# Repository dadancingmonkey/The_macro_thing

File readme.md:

a cool little macro pad for my desk!

This is sort of inspired by spotify's The Car Thing, hence the name. 

while I am familiar with my 3d modeling software, onshape, and i have been 3d printing for the past couple of months since i got my printer, this is my first project that involves electronics. 
This project was the first time i've ever used Kicad, and through following guides and tutorials on youtube, i was able to cobble together my own little macropad!

the assembly:

the top blue part is jsut a press fit:

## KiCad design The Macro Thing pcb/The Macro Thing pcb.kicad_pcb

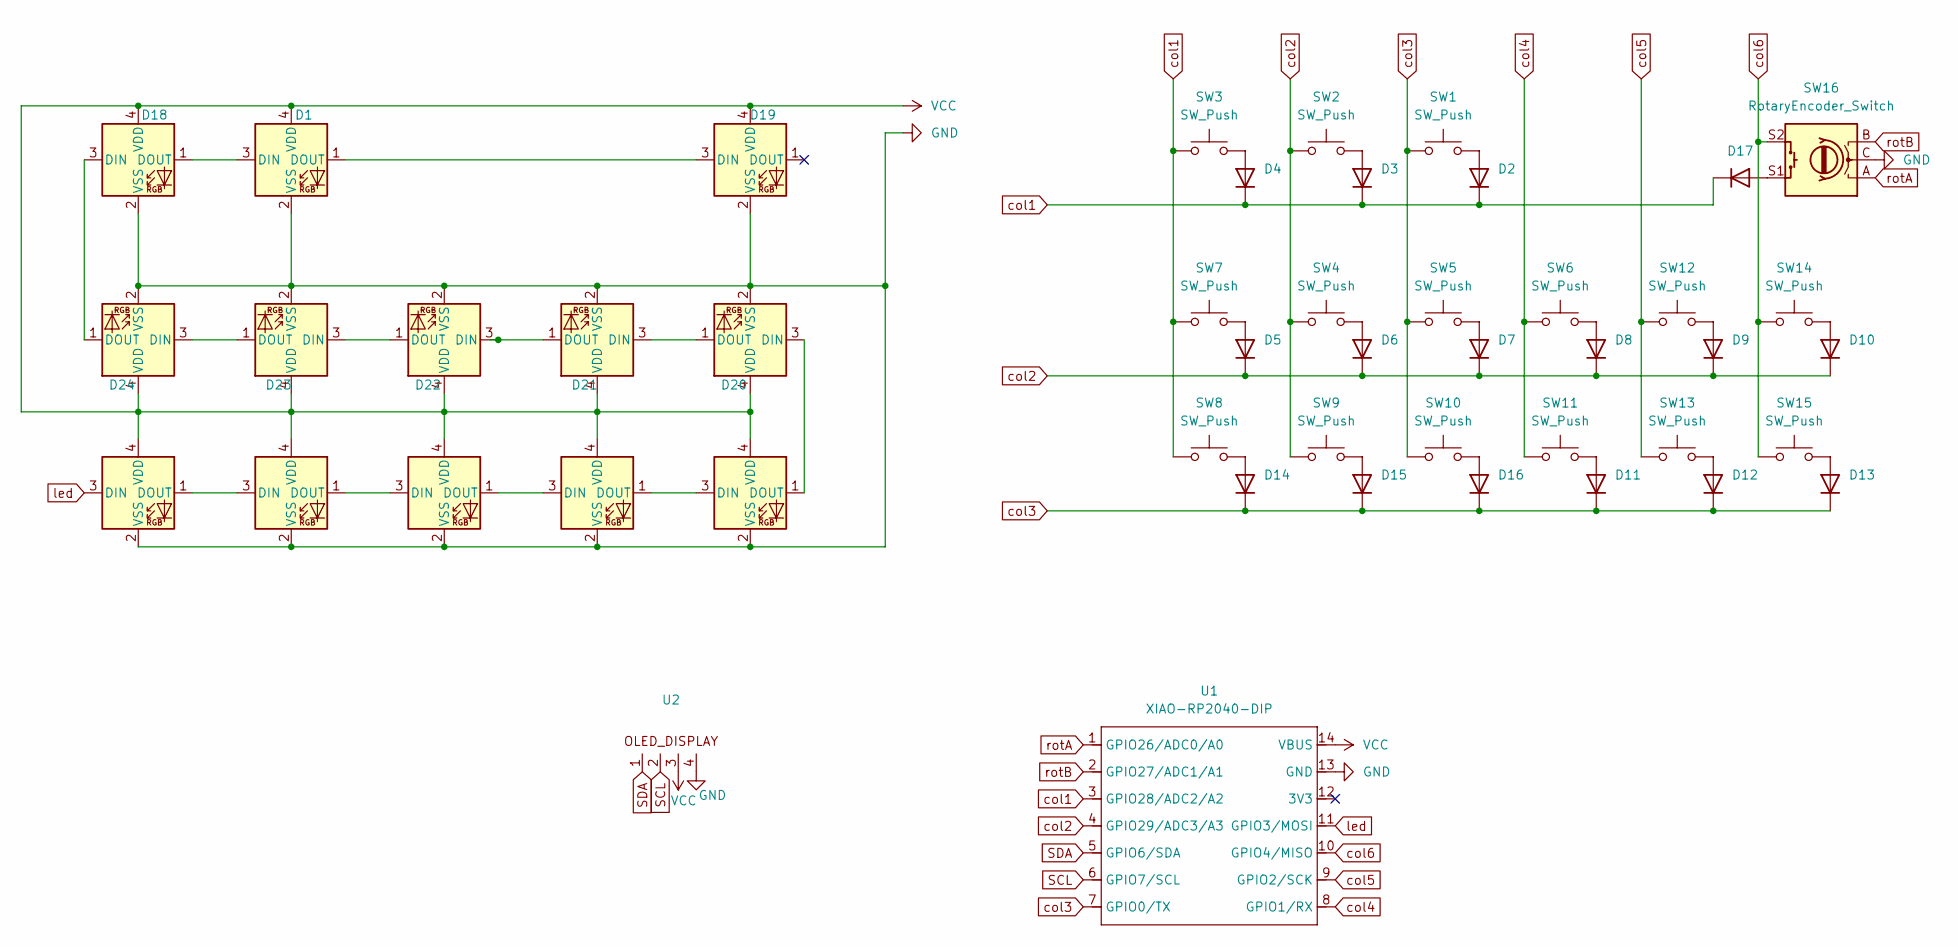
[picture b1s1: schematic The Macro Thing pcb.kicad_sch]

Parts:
D1, D18, D19, D20, D21, D22, D23, D24, D25, D26, D27, D28, D29: SK6812MINI; LED_SK6812MINI_PLCC4_3.5x3.5mm_P1.75mm
D2, D3, D4, D5, D6, D7, D8, D9, D10, D11, D12, D13, D14, D15, D16, D17: 1N4148WT; D_DO-35_SOD27_P7.62mm_Horizontal
SW1, SW2, SW3, SW4, SW5, SW6, SW7, SW8, SW9, SW10, SW11, SW12, SW13, SW14, SW15: SW_Push; SW_Cherry_MX_1.00u_PCB
SW16: RotaryEncoder_Switch; RotaryEncoder_Alps_EC11E-Switch_Vertical_H20mm
U1: XIAO-RP2040-DIP
U2: PinHeader_1x04_P2.54mm_Vertical

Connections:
GND: D1.2 (VSS), D18.2 (VSS), D19.2 (VSS), D20.2 (VSS), D21.2 (VSS), D22.2 (VSS), D23.2 (VSS), D24.2 (VSS), D25.2 (VSS), D26.2 (VSS), D27.2 (VSS), D28.2 (VSS), D29.2 (VSS), SW16.C, U1.13 (GND), U2.4
unnamed: D1.3 (DIN), D18.1 (DOUT)
unnamed: D1.1 (DOUT), D19.3 (DIN)
unnamed: D2.2 (A), SW1.2
unnamed: D3.2 (A), SW2.2
unnamed: D4.2 (A), SW3.2
unnamed: D5.2 (A), SW7.2
unnamed: D6.2 (A), SW4.2
unnamed: D7.2 (A), SW5.2
unnamed: D8.2 (A), SW6.2
unnamed: D9.2 (A), SW12.2
unnamed: D10.2 (A), SW14.2
unnamed: D11.2 (A), SW11.2
unnamed: D12.2 (A), SW13.2
unnamed: D13.2 (A), SW15.2
unnamed: D14.2 (A), SW8.2
unnamed: D15.2 (A), SW9.2
unnamed: D16.2 (A), SW10.2
unnamed: D17.2 (A), SW16.S1
unnamed: D18.3 (DIN), D24.1 (DOUT)
unnamed: D20.3 (DIN), D29.1 (DOUT)
unnamed: D20.1 (DOUT), D21.3 (DIN)
unnamed: D21.1 (DOUT), D22.3 (DIN)
unnamed: D22.1 (DOUT), D23.3 (DIN)
unnamed: D23.1 (DOUT), D24.3 (DIN)
unnamed: D25.1 (DOUT), D26.3 (DIN)
unnamed: D26.1 (DOUT), D27.3 (DIN)
unnamed: D27.1 (DOUT), D28.3 (DIN)
unnamed: D28.1 (DOUT), D29.3 (DIN)
SCL: U1.6 (GPIO7/SCL), U2.2
SDA: U1.5 (GPIO6/SDA), U2.1
VCC: D1.4 (VDD), D18.4 (VDD), D19.4 (VDD), D20.4 (VDD), D21.4 (VDD), D22.4 (VDD), D23.4 (VDD), D24.4 (VDD), D25.4 (VDD), D26.4 (VDD), D27.4 (VDD), D28.4 (VDD), D29.4 (VDD), U1.14 (VBUS), U2.3
col1: D2.1 (K), D3.1 (K), D4.1 (K), D17.1 (K), SW3.1, SW7.1, SW8.1, U1.3 (GPIO28/ADC2/A2)
col2: D5.1 (K), D6.1 (K), D7.1 (K), D8.1 (K), D9.1 (K), D10.1 (K), SW2.1, SW4.1, SW9.1, U1.4 (GPIO29/ADC3/A3)
col3: D11.1 (K), D12.1 (K), D13.1 (K), D14.1 (K), D15.1 (K), D16.1 (K), SW1.1, SW5.1, SW10.1, U1.7 (GPIO0/TX)
col4: SW6.1, SW11.1, U1.8 (GPIO1/RX)
col5: SW12.1, SW13.1, U1.9 (GPIO2/SCK)
col6: SW14.1, SW15.1, SW16.S2, U1.10 (GPIO4/MISO)
led: D25.3 (DIN), U1.11 (GPIO3/MOSI)
rotA: SW16.A, U1.1 (GPIO26/ADC0/A0)
rotB: SW16.B, U1.2 (GPIO27/ADC1/A1)

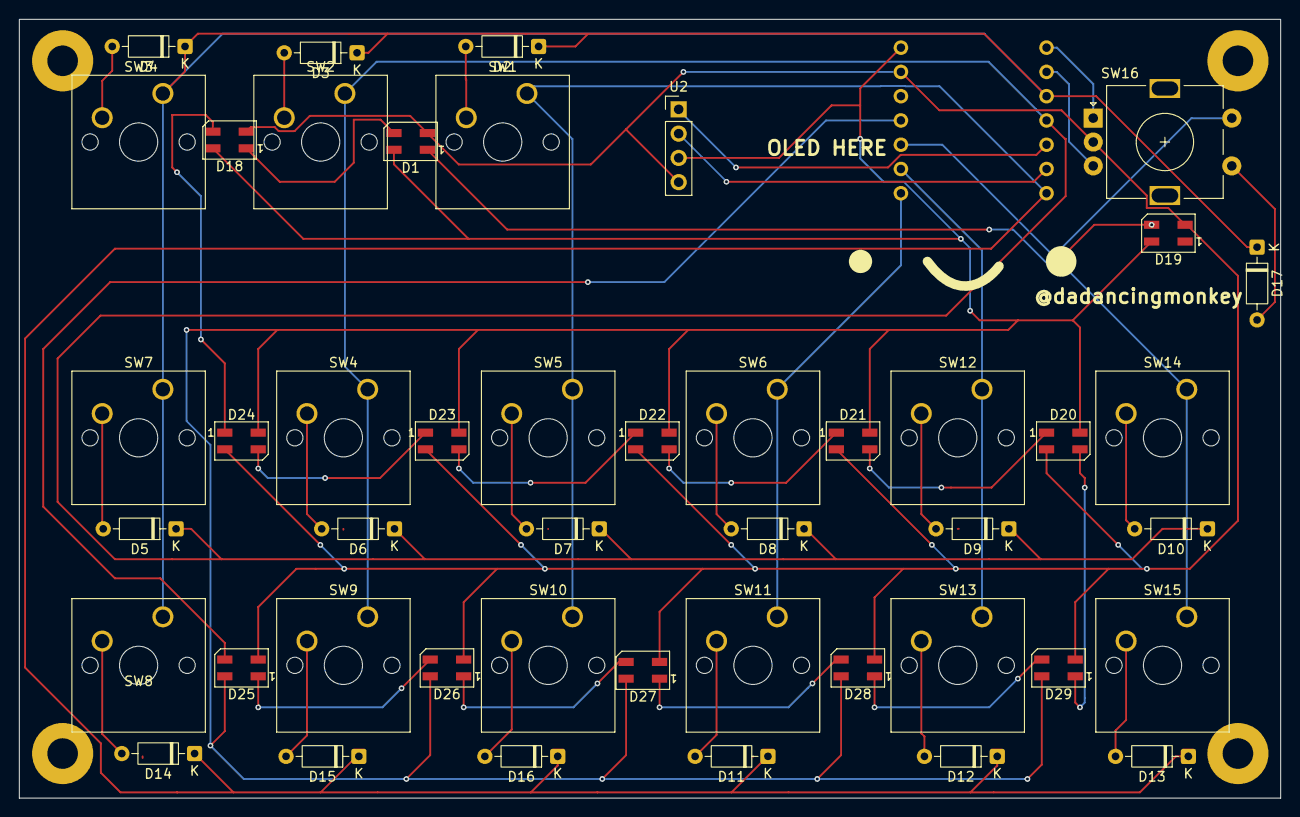
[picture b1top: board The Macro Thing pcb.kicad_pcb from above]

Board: 2 copper layers, 132.0 x 81.5 mm, 47 parts (1 on the bottom side), 41 nets.

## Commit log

2025-12-26 rname cad
2025-12-26 Add initial macro code for QMK firmware
2025-12-27 assembly added
    i think this is what you wanted? im not quite sure by what was meant by add an assembly
2025-12-27 code file
2025-12-27 renamed
2025-12-27 Add description for macro pad project
2025-12-27 add images
2025-12-27 more to readme
2025-12-27 added pcb and screws
2025-12-27 fixed mistakes
2025-12-27 added images
